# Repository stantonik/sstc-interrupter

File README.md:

# SSTC-Interrupter

> Digital interrupter for driving SSTC/DRSSTC Tesla coils, built around the ESP32-S3.
Easily customizable and extensible thanks to the microcontroller platform.

**Actually in development!**

## Overview

This project implements a digital interrupter for Solid State Tesla Coils (SSTC) or Dual-Resonant SSTCs (DRSSTC). The interrupter allows precise control over the arc output using different control modes, making it easy to experiment with pulse timing, audio modulation, or MIDI control.

## Hardware Highlights

- Microcontroller: ESP32-S3 - powerful, friendly SDK, and USB-OTG.
- Isolation: Fiber-optic input using TOSLINK transceivers. Safe and affordable alternative to Broadcom HFBR14xx/24xx.
- Cost-effective: Total BOM under 20 €, including ESP32-S3, TOSLINK modules, and basic passive components.
- User interface: 164×64 OLED screen (running LVGL) with rotary encoder.
- Connectivity:
  - 3.5 mm line-in for audio modulation.
  - USB-OTG (serial, MIDI, ...)
  - TOSLINK/pin header outputs

## Features

**1. Manual Mode**

- Control three parameters directly using knobs:
  - Pulse Duration (PD) – width of each pulse.
  - Pulse Repetition Frequency (PRF) – pulse frequency.
  - Power – proportional to PD.
- Generates PWM signals from 1 Hz up to 20 kHz with a minimum pulse width of 1 µs.
- Ideal for manual experimentation and tuning the arc.WM carrier frequency is 30KHz by default, but you can adjust these value to fit your needs.

The signal generated is supposed to be ANDed with your main Tesla drive signal.

**2. Audio (Line-In) Mode**

- Connect any audio source via a 3.5 mm jack.
- Audio is sampled at 16 kHz and used to modulate the PWM output.
- Default PWM carrier frequency is 30 kHz, adjustable to match your Tesla coil system.
- Supports basic PWM modulation for now, but can be extended for other modulation schemes.

**3. MIDI Mode**

- Connect a MIDI device to control the arc in real time.
- Map MIDI notes to pulse patterns for musical performance with your Tesla coil.

## Notes

- The output of this module is intended to be ANDed with your main Tesla coil drive signal.
- All modes are fully software-driven on the ESP32-S3, making it easy to customize, extend, or add new modulation features.

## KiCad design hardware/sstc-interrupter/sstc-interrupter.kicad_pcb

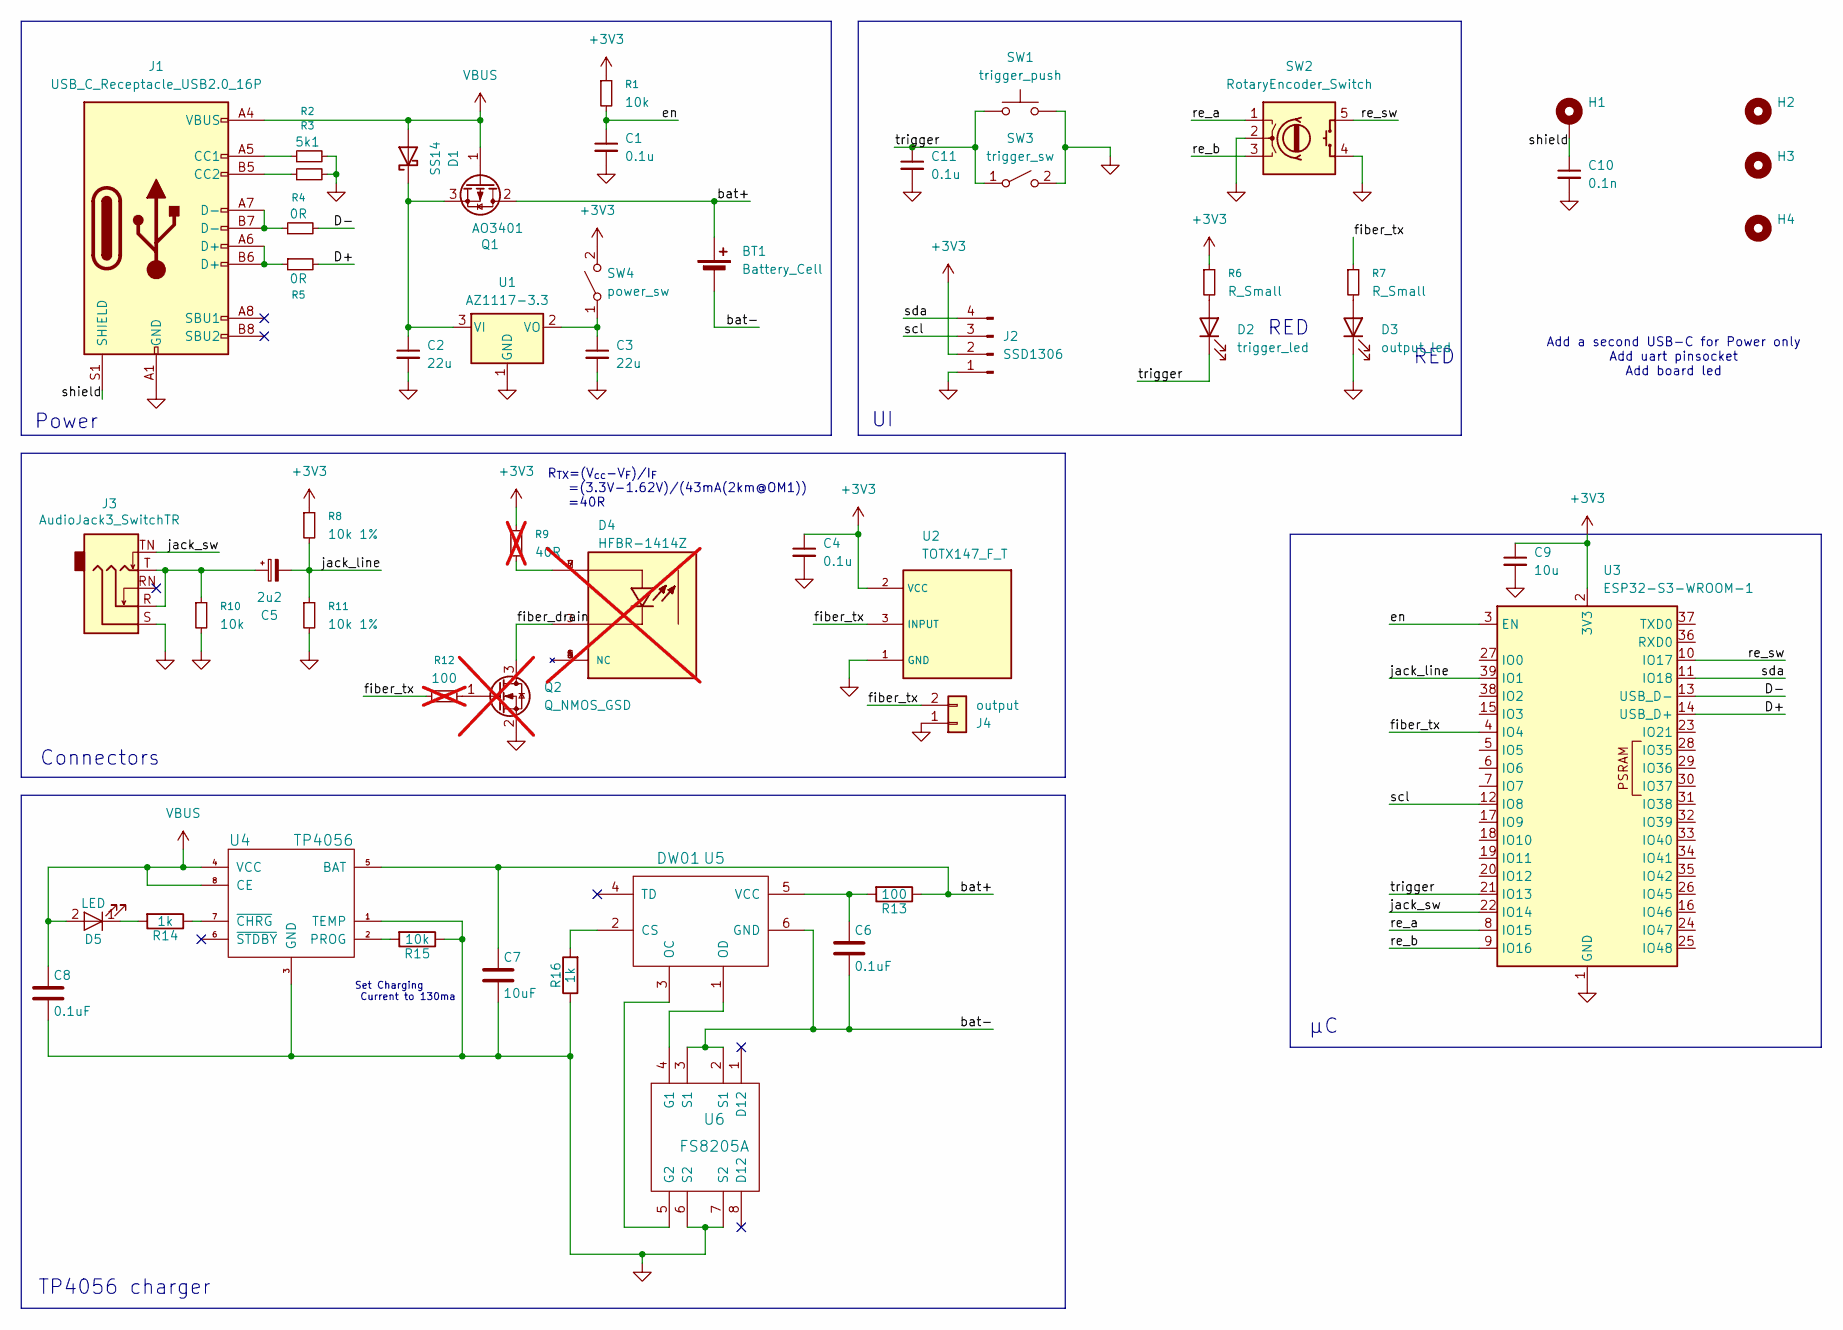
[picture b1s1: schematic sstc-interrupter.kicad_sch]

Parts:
BT1: Battery_Cell; JST_PH_B2B-PH-K_1x02_P2.00mm_Vertical
C1, C4, C11: 0.1u; C_0603_1608Metric_Pad1.08x0.95mm_HandSolder
C2, C3: 22u; C_0805_2012Metric_Pad1.18x1.45mm_HandSolder
C5: 2u2; C_Radial_D5.0mm_H11.0mm_P2.00mm
C6, C8: 0.1uF; C_0603_1608Metric_Pad1.08x0.95mm_HandSolder
C7: 10uF; C_0603_1608Metric_Pad1.08x0.95mm_HandSolder
C9: 10u; C_0805_2012Metric_Pad1.18x1.45mm_HandSolder
C10: 0.1n; C_0805_2012Metric_Pad1.18x1.45mm_HandSolder
D1: SS14; D_SMA
D2: trigger_led; PinHeader_1x02_P2.54mm_Vertical
D3: output_led; PinHeader_1x02_P2.54mm_Vertical
D4: HFBR-1414Z; OPTO_HFBR-1414Z; PARTREV February 15, 2019; not fitted
D5: LED; LED_0603_1608Metric_Pad1.05x0.95mm_HandSolder
H1: MountingHole_Pad; MountingHole_2.2mm_M2_DIN965_Pad
H2, H3, H4: MountingHole; MountingHole_2.2mm_M2_DIN965
J1: USB_C_Receptacle_USB2.0_16P; USB_C_Receptacle_GCT_USB4105-xx-A_16P_TopMnt_Horizontal
J2: SSD1306; PinHeader_1x04_P2.54mm_Vertical
J3: AudioJack3_SwitchTR; Jack_3.5mm_CUI_SJ1-3525N_Horizontal
J4: output; PinHeader_1x02_P2.54mm_Horizontal
Q1: AO3401; SOT-23_Handsoldering
Q2: Q_NMOS_GSD; SOT-23-3; not fitted
R1, R10, R15: 10k; R_0603_1608Metric_Pad0.98x0.95mm_HandSolder
R2, R3: 5k1; R_0603_1608Metric_Pad0.98x0.95mm_HandSolder
R4, R5: 0R; R_0603_1608Metric_Pad0.98x0.95mm_HandSolder
R6, R7: R_Small; R_0603_1608Metric_Pad0.98x0.95mm_HandSolder
R8, R11: 10k 1%; R_0603_1608Metric_Pad0.98x0.95mm_HandSolder
R9: 40R; R_0603_1608Metric_Pad0.98x0.95mm_HandSolder; not fitted
R12: 100; R_0603_1608Metric_Pad0.98x0.95mm_HandSolder; not fitted
R13: 100; R_0603_1608Metric_Pad0.98x0.95mm_HandSolder
R14, R16: 1k; R_0603_1608Metric_Pad0.98x0.95mm_HandSolder
SW1: trigger_push; PinHeader_1x02_P2.54mm_Vertical
SW2: RotaryEncoder_Switch; PinHeader_1x05_P2.54mm_Vertical
SW3: trigger_sw; PinHeader_1x02_P2.54mm_Vertical
SW4: power_sw; PinHeader_1x02_P2.54mm_Vertical
U1: AZ1117-3.3; SOT-89-3
U2: TOTX147_F_T; TOSHIBA_TORX147_F_T_
U3: ESP32-S3-WROOM-1; ESP32-S3-WROOM-1U
U4: TP4056; SOP-8_3.9x4.9mm_P1.27mm
U5: DW01; SOT-23-6_Handsoldering
U6: FS8205A; TSSOP-8_4.4x3mm_P0.65mm

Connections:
+3V3: C4.1, C9.1, J2.2, R1.1, R6.1, R8.1, R9.1, SW4.2 (B), U2.2 (VCC), U3.2 (3V3)
/D+: R5.2, U3.14 (USB_D+)
/D-: R4.2, U3.13 (USB_D-)
/bat+: BT1.1 (+), C7.1, Q1.2 (D), R13.1, U4.5 (BAT)
/bat-: BT1.2 (-), C6.2, U5.6 (GND), U6.2 (S1), U6.3 (S1)
/en: C1.1, R1.2, U3.3 (EN)
/fiber_tx: J4.2, R7.1, R12.1, U2.3 (INPUT), U3.4 (IO4)
/jack_line: C5.2, R8.2, R11.1, U3.39 (IO1)
/jack_sw: J3.TN, U3.22 (IO14)
/re_a: SW2.1 (A), U3.8 (IO15)
/re_b: SW2.3 (B), U3.9 (IO16)
/re_sw: SW2.5 (S1), U3.10 (IO17)
/scl: J2.3, U3.12 (IO8)
/sda: J2.4, U3.11 (IO18)
/shield: C10.1, H1.1, J1.S1 (SHIELD)
/trigger: C11.1, D2.1 (K), SW1.1, SW3.1 (A), U3.21 (IO13)
GND: C1.2, C2.2, C3.2, C4.2, C7.2, C8.2, C9.2, C10.2, C11.2, D3.1 (K), J1.A1 (GND), J1.A12 (GND), J1.B1 (GND), J1.B12 (GND), J2.1, J3.S, J4.1, Q2.2 (S), R2.2, R3.2, R10.2, R11.2, R15.1, R16.1, SW1.2, SW2.2 (C), SW2.4 (S2), SW3.2 (B), U1.1 (GND), U2.1 (GND), U3.1 (GND), U3.40 (GND), U3.41 (GND), U4.1 (TEMP), U4.3 (GND), U6.6 (S2), U6.7 (S2)
unnamed: C5.1, J3.R, J3.T, R10.1
unnamed: C2.1, D1.1 (K), Q1.3 (S), U1.3 (VI)
unnamed: D2.2 (A), R6.2
unnamed: D3.2 (A), R7.2
unnamed: D4.1 (NC), D4.4 (NC), D4.5 (NC), D4.8 (NC)
unnamed: D4.2, D4.6, D4.7, R9.2
unnamed: D4.3, Q2.3 (D)
unnamed: D5.1 (K), R14.2
unnamed: J1.A5 (CC1), R2.1
unnamed: J1.B5 (CC2), R3.1
unnamed: J1.A6 (D+), J1.B6 (D+), R5.1
unnamed: J1.A7 (D-), J1.B7 (D-), R4.1
unnamed: Q2.1 (G), R12.2
unnamed: C3.1, SW4.1 (A), U1.2 (VO)
unnamed: R15.2, U4.2 (PROG)
unnamed: R14.1, U4.7 (~CHRG)
unnamed: R16.2, U5.2 (CS)
unnamed: U5.3 (OC), U6.5 (G2)
unnamed: U5.1 (OD), U6.4 (G1)
unnamed: C6.1, R13.2, U5.5 (VCC)
VBUS: C8.1, D1.2 (A), D5.2 (A), J1.A4 (VBUS), J1.A9 (VBUS), J1.B4 (VBUS), J1.B9 (VBUS), Q1.1 (G), U4.4 (VCC), U4.8 (CE)

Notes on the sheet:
Add a second USB-C for Power only Add uart pinsocket Add board led
Set Charging Current to 130ma
Connectors
R_{TX}=(V_{cc}-V_{F})/I_{F} =(3.3V-1.62V)/(43mA(2km@OM1)) =40R
RED
Power
TP4056 charger

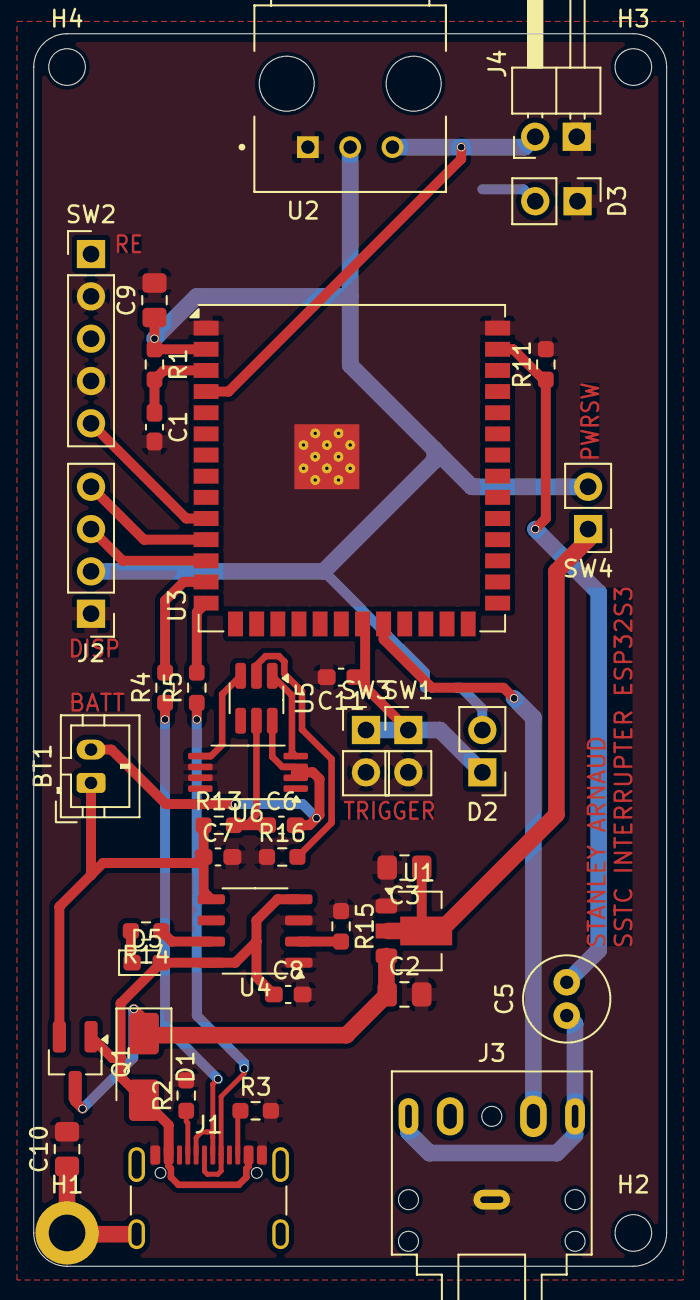
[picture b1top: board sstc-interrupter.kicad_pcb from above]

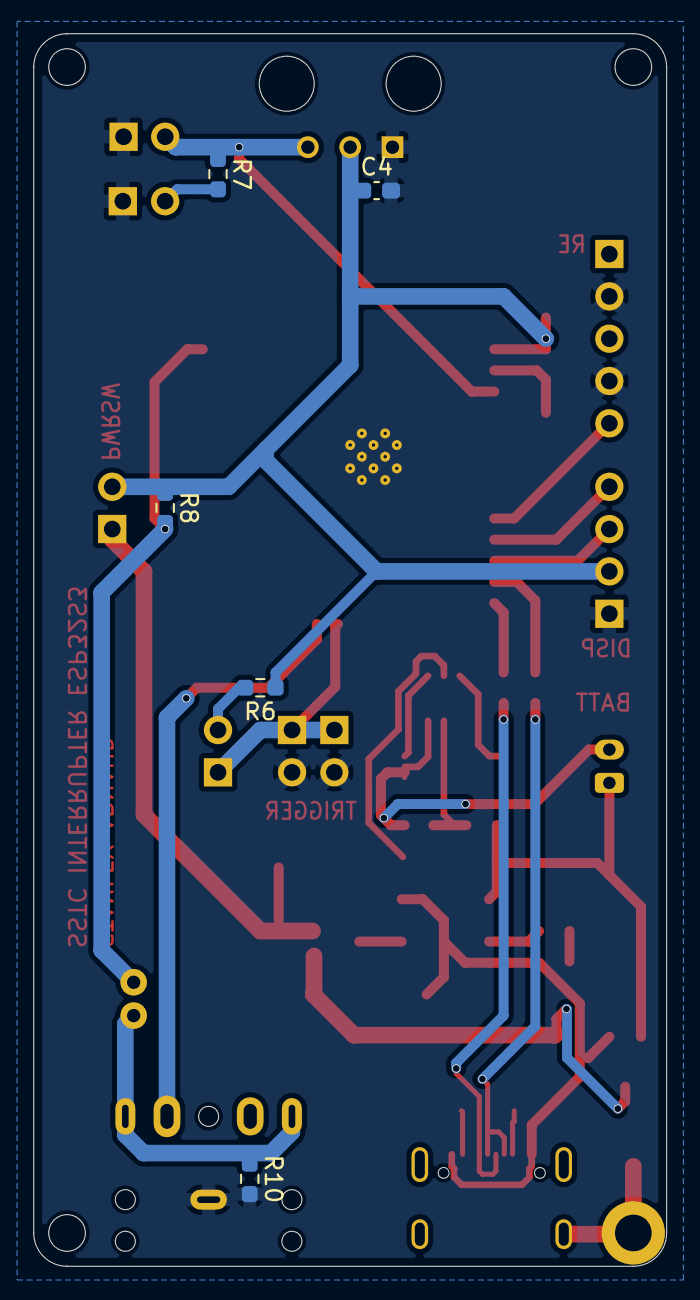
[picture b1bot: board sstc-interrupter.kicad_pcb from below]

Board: 2 copper layers, 38.0 x 74.0 mm, 49 parts (5 on the bottom side), 34 nets.

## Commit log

2025-09-26 base commit
2025-10-02 add kicad
2025-10-02 begin midi
2025-10-02 update readme and gitignore
